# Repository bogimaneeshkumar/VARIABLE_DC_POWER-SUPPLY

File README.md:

# AC to DC Variable Power Supply

This project is a variable power supply that converts alternating current (AC) from a household power source into direct current (DC). The user can adjust the output voltage, which allows for the adjustment of the power drawn based on their specific requirements. The power supply is equipped with a built-in voltage sensing mechanism that displays the real-time voltage on an LED screen by help of flash kind of ADC method and the BCD to 7segment decoder and the 7 segment LED.

## Features

- Variable output voltage: The user can adjust the output voltage within a range of 1V to 19V.
- Adjustable power rating: The power supply can be used as a variable charger, providing adjustable power output.
- Real-time voltage display: The voltage being supplied is continuously monitored and displayed on the LED screen.
- C-type pin output: The power supply is equipped with a C-type pin output, making it compatible with a wide range of devices.
- Maximum current limit: The maximum current that can be drawn from the power supply is 3A.

## Future Enhancements

In the future, the project can be further improved with the following modifications:

- Variable current output: By making additional modifications to the circuit, the power supply can also provide variable current output.
- Voltage and current sensing: The circuit can be enhanced to sense both voltage and current, allowing for more precise control and monitoring.
- Increased voltage range: The range of adjustable voltage can be expanded beyond the current limit of 1V to 19V, catering to a wider range of applications.

## Usage

To use the AC to DC Variable Power Supply, follow these steps:

1. Connect the power supply to an AC household power source.
2. Adjust the desired output voltage using the provided controls.
3. Connect your device to the power supply using the C-type pin.
4. Monitor the real-time voltage on the LED screen.
5. Ensure the drawn current does not exceed the maximum limit of 3A.

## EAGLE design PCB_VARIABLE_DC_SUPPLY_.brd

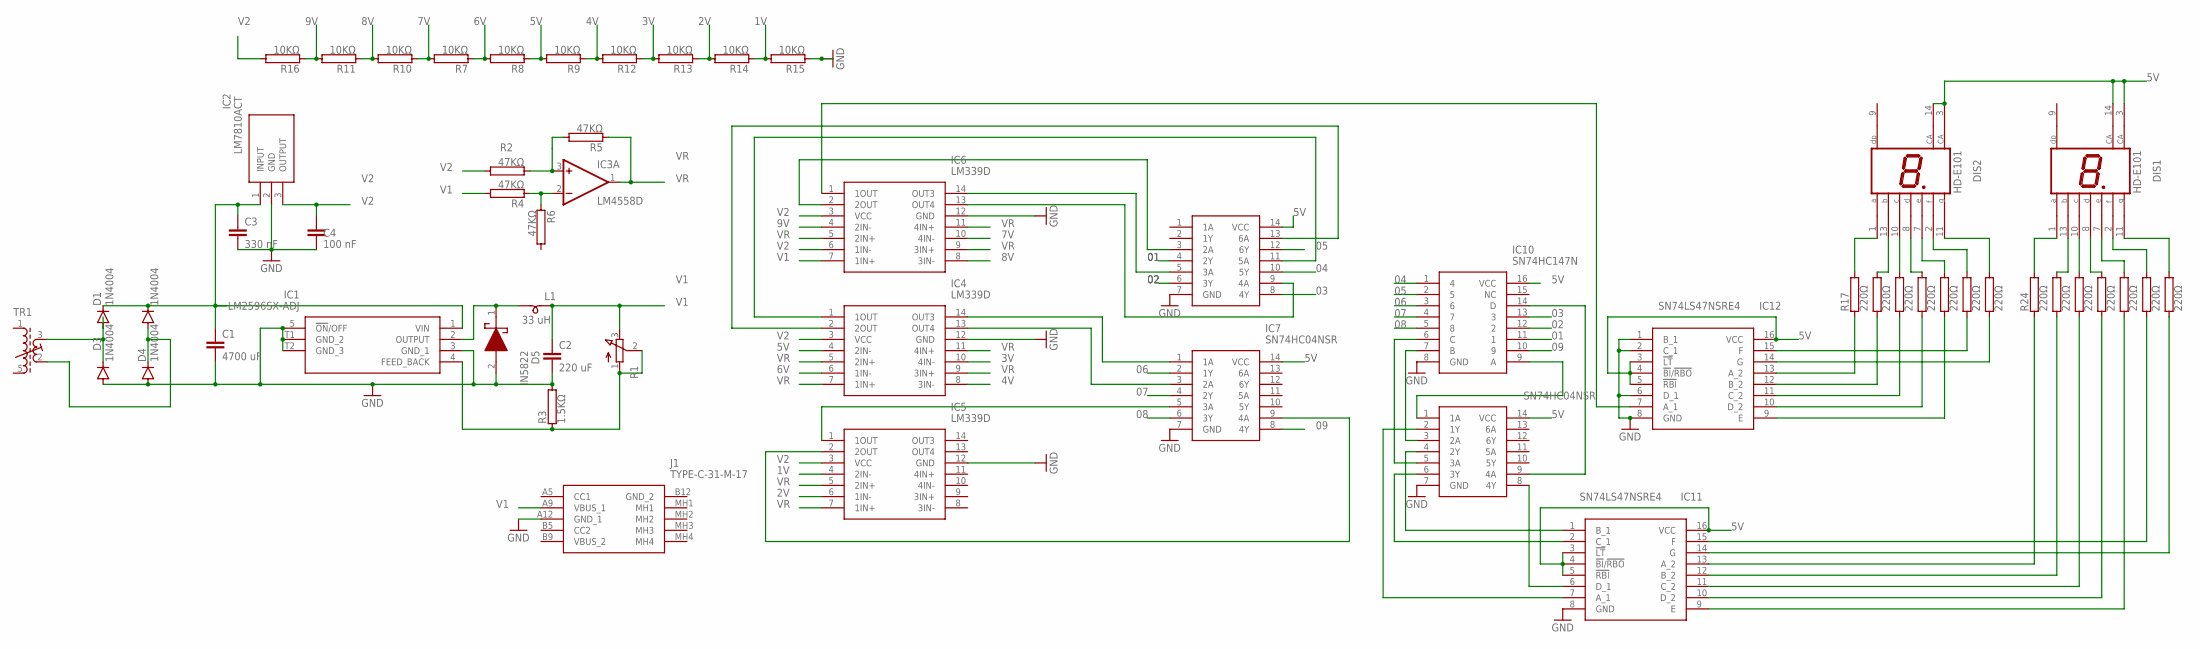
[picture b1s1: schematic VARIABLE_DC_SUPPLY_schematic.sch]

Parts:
C1: 4700 uF; C2.5-2
C2: 220 uF; C2.5-2
C3: 330 nF; C2.5-2
C4: 100 nF; C2.5-2
D1, D2, D3, D4: 1N4004; DO41-10
D5: IN5822; DIOAD3020W130L900D530
DIS1, DIS2: HD-E101; HDSP-I
IC1: LM2596SX-ADJ; LM2596SXADJ
IC2: LM7810ACT; TO254P470X1016X2019-3P
IC3: LM4558D; SO08
IC4, IC5, IC6: LM339D; SOIC127P600X175-14N
IC7, IC8, IC9: SN74HC04NSR; SOIC127P780X200-14N
IC10: SN74HC147N; DIP794W53P254L1930H508Q16N
IC11, IC12: SN74LS47NSRE4; SOIC127P780X200-16N
J1: TYPE-C-31-M-17; TYPEC31M17
L1: 33 uH; SM-B5
R1: 3RP/1610N
R2, R4, R5, R6: 47KΩ; TO-247-2V
R3: 1.5KΩ; TO-247-2V
R7, R8, R9, R10, R11, R12, R13, R14, R15, R16: 10KΩ; TO-247-2V
R17, R18, R19, R20, R21, R22, R23, R24, R25, R26, R27, R28, R29, R30: 220Ω; TO-247-2V
TR1: 71-4-1532; 71-5

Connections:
01: IC8.4 (2Y), IC10.11 (1)
1V: IC5.4 (2IN-), R14.1, R15.2
02: IC8.6 (3Y), IC10.12 (2)
2V: IC5.6 (1IN-), R13.1, R14.2
03: IC8.8 (4Y), IC10.13 (3)
3V: IC4.10 (4IN-), R12.1, R13.2
04: IC8.10 (5Y), IC10.1 (4)
4V: IC4.8 (3IN-), R9.1, R12.2
05: IC8.12 (6Y), IC10.2 (5)
5V: DIS1.3 (CA), DIS1.14 (CA), DIS2.3 (CA), DIS2.14 (CA), IC4.4 (2IN-), IC7.14 (VCC), IC8.14 (VCC), IC9.14 (VCC), IC10.16 (VCC), IC11.3 (!LT), IC11.4 (!BI!/!RBO), IC11.5 (!RBI), IC11.16 (VCC), IC12.3 (!LT), IC12.4 (!BI!/!RBO), IC12.5 (!RBI), IC12.16 (VCC), R8.1, R9.2
06: IC7.2 (1Y), IC10.3 (6)
6V: IC4.6 (1IN-), R7.1, R8.2
07: IC7.4 (2Y), IC10.4 (7)
7V: IC6.10 (4IN-), R7.2, R10.1
08: IC7.6 (3Y), IC10.5 (8)
8V: IC6.8 (3IN-), R10.2, R11.1
09: IC7.8 (4Y), IC10.10 (9)
9V: IC6.4 (2IN-), R11.2, R16.1
GND: C1.2, C2.2, C3.2, C4.2, D3.A, D4.A, D5.2 (A), IC1.3 (GND_1), IC1.5 (!ON!/OFF), IC1.T1 (GND_2), IC1.T2 (GND_3), IC2.2 (GND), IC4.12 (GND), IC5.12 (GND), IC6.12 (GND), IC7.7 (GND), IC8.7 (GND), IC9.7 (GND), IC10.8 (GND), IC11.8 (GND), IC12.1 (B_1), IC12.2 (C_1), IC12.6 (D_1), IC12.8 (GND), J1.A12 (GND_1), R3.2, R15.1
unnamed: D1.A, D3.C, TR1.3 (A2)
unnamed: D2.A, D4.C, TR1.2 (E2)
unnamed: D5.1 (K), IC1.2 (OUTPUT), L1.1
unnamed: C1.1, C3.1, D1.C, D2.C, IC1.1 (VIN), IC2.1 (INPUT)
unnamed: IC3.3 (+IN), R2.1, R5.2
unnamed: IC1.4 (FEED_BACK), R1.1 (A), R1.2 (S), R3.1
unnamed: IC3.2 (-IN), R4.1, R6.1
unnamed: IC6.2 (2OUT), IC8.3 (2A)
unnamed: IC6.14 (OUT3), IC8.5 (3A)
unnamed: IC6.13 (OUT4), IC8.9 (4A)
unnamed: IC4.1 (1OUT), IC8.11 (5A)
unnamed: IC4.2 (2OUT), IC8.13 (6A)
unnamed: IC4.14 (OUT3), IC7.1 (1A)
unnamed: IC4.13 (OUT4), IC7.3 (2A)
unnamed: IC5.1 (1OUT), IC7.5 (3A)
unnamed: IC5.2 (2OUT), IC7.9 (4A)
unnamed: IC9.1 (1A), IC10.9 (A)
unnamed: IC9.3 (2A), IC10.7 (B)
unnamed: IC9.5 (3A), IC10.6 (C)
unnamed: IC9.9 (4A), IC10.14 (D)
unnamed: DIS2.1 (A), R17.2
unnamed: IC6.1 (1OUT), IC12.7 (A_1)
unnamed: IC9.2 (1Y), IC11.7 (A_1)
unnamed: IC9.4 (2Y), IC11.1 (B_1)
unnamed: IC9.6 (3Y), IC11.2 (C_1)
unnamed: IC9.8 (4Y), IC11.6 (D_1)
unnamed: DIS2.13 (B), R18.2
unnamed: DIS2.10 (C), R19.2
unnamed: DIS2.8 (D), R20.2
unnamed: DIS2.2 (F), R22.2
unnamed: DIS2.7 (E), R21.2
unnamed: DIS2.11 (G), R23.2
unnamed: DIS1.10 (C), R26.2
unnamed: DIS1.1 (A), R24.2
unnamed: DIS1.13 (B), R25.2
unnamed: DIS1.8 (D), R27.2
unnamed: DIS1.7 (E), R28.2
unnamed: DIS1.2 (F), R29.2
unnamed: DIS1.11 (G), R30.2
unnamed: IC12.13 (A_2), R17.1
unnamed: IC12.12 (B_2), R18.1
unnamed: IC12.11 (C_2), R19.1
unnamed: IC12.10 (D_2), R20.1
unnamed: IC12.9 (E), R21.1
unnamed: IC12.15 (F), R22.1
unnamed: IC12.14 (G), R23.1
unnamed: IC11.13 (A_2), R24.1
unnamed: IC11.12 (B_2), R25.1
unnamed: IC11.11 (C_2), R26.1
unnamed: IC11.10 (D_2), R27.1
unnamed: IC11.9 (E), R28.1
unnamed: IC11.15 (F), R29.1
unnamed: IC11.14 (G), R30.1
V1: C2.1, IC6.7 (1IN+), J1.A9 (VBUS_1), L1.2, R1.3 (E), R4.2
V2: C4.1, IC2.3 (OUTPUT), IC4.3 (VCC), IC5.3 (VCC), IC6.3 (VCC), IC6.6 (1IN-), R2.2, R16.2
V+: IC3.8 (V+)
V-: IC3.4 (V-)
VR: IC3.1 (OUT), IC4.5 (2IN+), IC4.7 (1IN+), IC4.9 (3IN+), IC4.11 (4IN+), IC5.5 (2IN+), IC5.7 (1IN+), IC6.5 (2IN+), IC6.9 (3IN+), IC6.11 (4IN+), R5.1

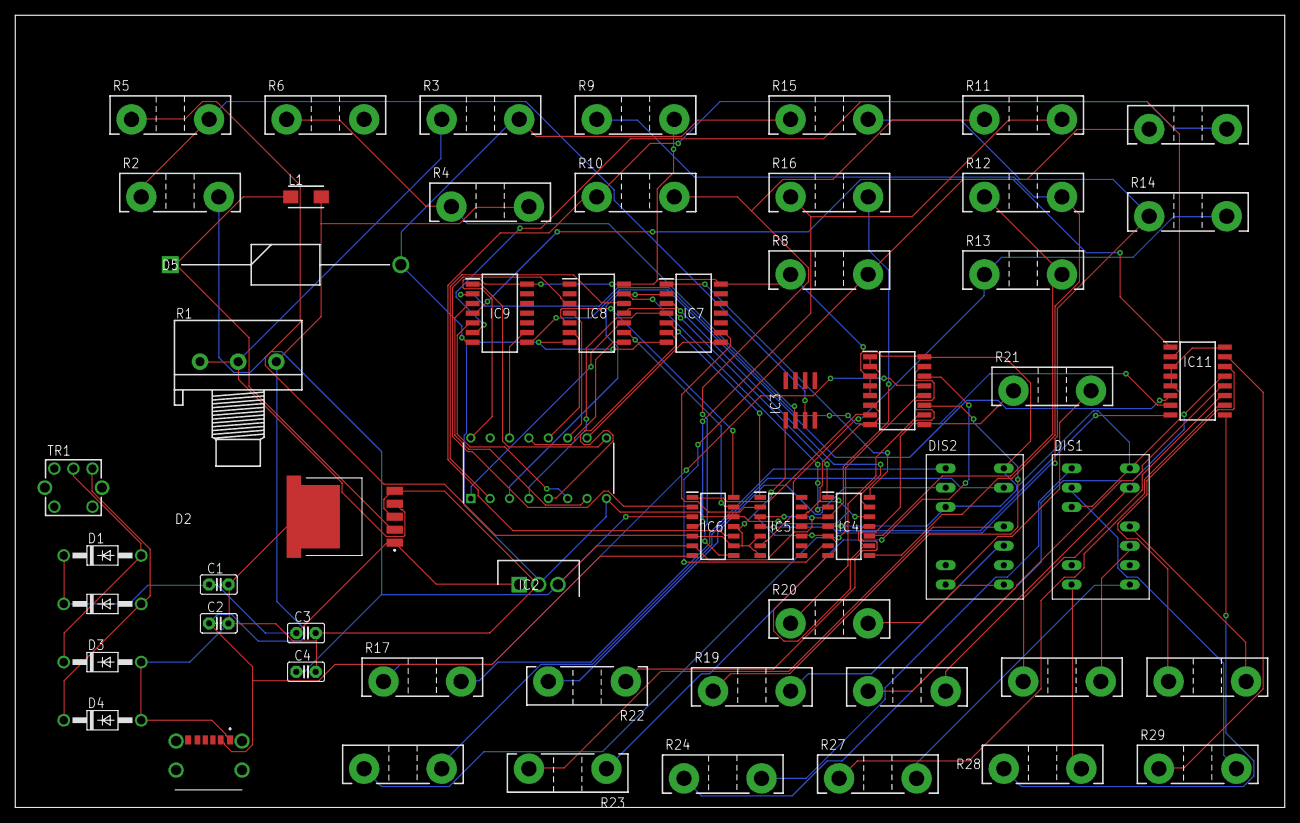
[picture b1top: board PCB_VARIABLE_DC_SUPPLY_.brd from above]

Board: 2 copper layers, 166.3 x 103.8 mm, 56 parts (0 on the bottom side), 75 nets.
